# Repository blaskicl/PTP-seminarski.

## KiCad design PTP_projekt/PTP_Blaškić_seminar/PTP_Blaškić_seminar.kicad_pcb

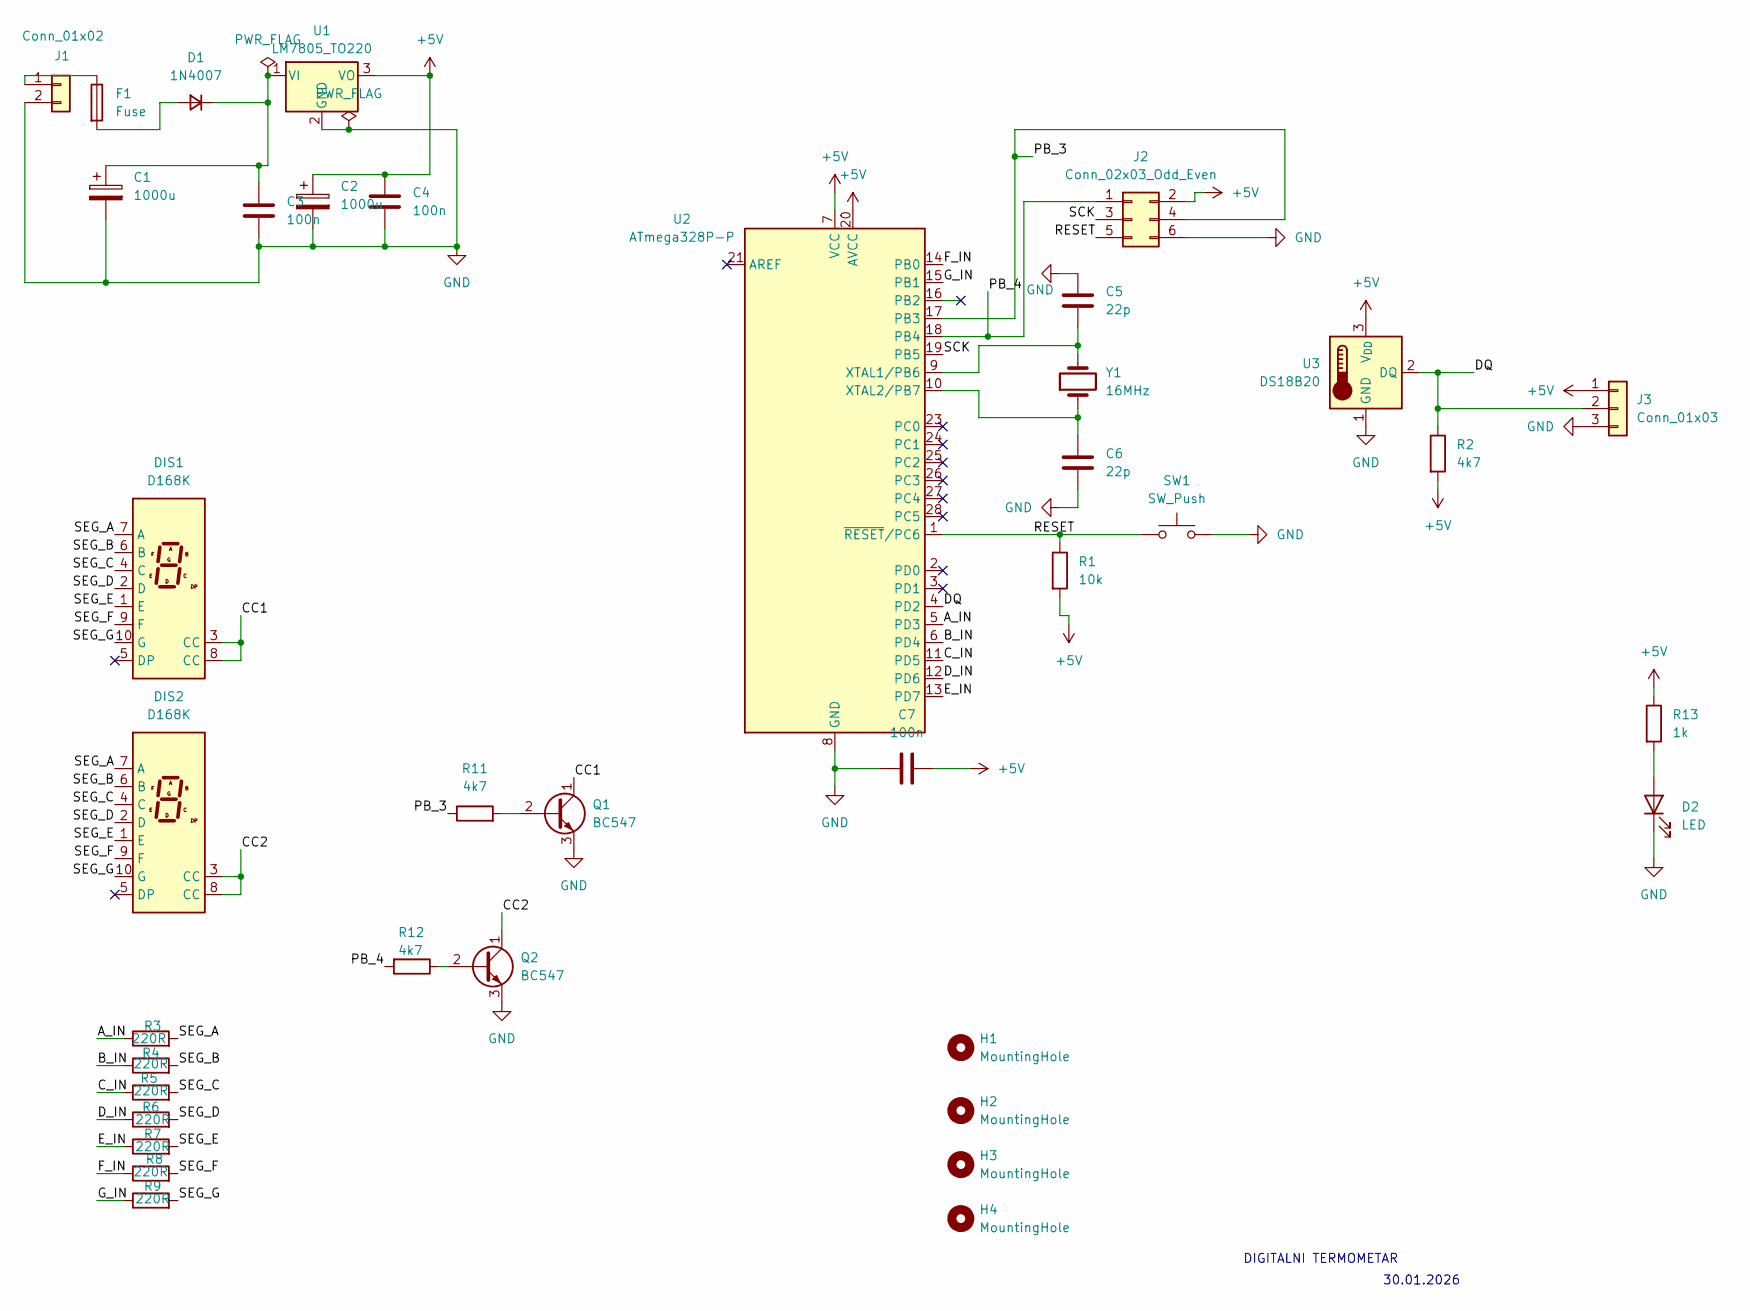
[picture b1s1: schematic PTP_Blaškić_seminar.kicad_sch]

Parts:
C1, C2: 1000u; CP_Radial_D10.0mm_P5.00mm; Manufacturers Part Numb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 UPM1V102MHD
C3, C4, C7: 100n; C_Disc_D5.0mm_W2.5mm_P5.00mm; Manufacturers Part Numb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 C315C104M5U5TA
C5, C6: 22p; C_Disc_D3.0mm_W1.6mm_P2.50mm; Manufacturers Part Numb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 RDE5C1H220J 0P1H03B
D1: 1N4007; D_DO-41_SOD81_P7.62mm_Horizontal; Manufacturers Part Numb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 1N4007-E3/54
D2: LED; LED_D5.0mm; Manufacturers Part Numb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 WP7113ID
DIS1, DIS2: D168K; D1X8K; Manufacturers Part Numb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 SC56-11EWA
F1: Fuse; Fuseholder_Cylinder-5x20mm_Bulgin_FX0457_Horizontal_Closed; Manufacturers Part Numb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 0218001.HXP
H1, H2, H3, H4: MountingHole; MountingHole_3.2mm_M3
J1: Conn_01x02; PinHeader_1x02_P2.54mm_Vertical; Manufacturers Part Numb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 TSW-102-07-G-S
J2: Conn_02x03_Odd_Even; PinHeader_2x03_P2.54mm_Vertical; Manufacturers Part Numb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 TSW-103-07-G-D
J3: Conn_01x03; PinHeader_1x03_P2.54mm_Vertical; Manufacturers Part Numb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 TSW-103-07-G-S
Q1, Q2: BC547; TO-92_Inline; Manufacturers Part Numb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 BC547B
R1: 10k; R_Axial_DIN0207_L6.3mm_D2.5mm_P10.16mm_Horizontal; Manufacturers Part Numb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 CFR-25JB-52-10K
R2, R11, R12: 4k7; R_Axial_DIN0207_L6.3mm_D2.5mm_P10.16mm_Horizontal; Manufacturers Part Numb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 CFR-25JB-52-4K7
R3, R4, R5, R6, R7, R8, R9: 220R; R_Axial_DIN0207_L6.3mm_D2.5mm_P10.16mm_Horizontal; Manufacturers Part Numb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 CFR-25JB-52-220R
R13: 1k; R_Axial_DIN0207_L6.3mm_D2.5mm_P10.16mm_Horizontal; Manufacturers Part Numb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 CFR-25JB-52-1K
SW1: SW_Push; SW_PUSH_6mm_H4.3mm; Manufacturers Part Numb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 B3F-1000
U1: LM7805_TO220; TO-220-3_Vertical; Manufacturers Part Numb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 L7805CV
U2: ATmega328P-P; DIP-28_W7.62mm; Manufacturers Part Numb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 ATMEGA328P-PU
U3: DS18B20; TO-92_Inline; Manufacturers Part Numb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 DS18B20+
Y1: 16MHz; Crystal_HC49-U_Vertical; Manufacturers Part Numb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 FA-238 16.0000MB-C3

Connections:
+5V: C2.1, C4.1, C7.2, J2.2, J3.1, R1.2, R2.2, R13.1, U1.3 (VO), U2.7 (VCC), U2.20 (AVCC), U3.3 (V_{DD})
/A_IN: R3.1, U2.5 (PD3)
/B_IN: R4.1, U2.6 (PD4)
/CC1: DIS1.3 (CC), DIS1.8 (CC), Q1.1 (C)
/CC2: DIS2.3 (CC), DIS2.8 (CC), Q2.1 (C)
/C_IN: R5.1, U2.11 (PD5)
/DQ: J3.2, R2.1, U2.4 (PD2), U3.2 (DQ)
/D_IN: R6.1, U2.12 (PD6)
/E_IN: R7.1, U2.13 (PD7)
/F_IN: R8.1, U2.14 (PB0)
/G_IN: R9.1, U2.15 (PB1)
/PB_3: J2.4, R11.1, U2.17 (PB3)
/PB_4: J2.1, R12.2, U2.18 (PB4)
/RESET: J2.5, R1.1, SW1.1, U2.1 (~RESET/PC6)
/SCK: J2.3, U2.19 (PB5)
/SEG_A: DIS1.7 (A), DIS2.7 (A), R3.2
/SEG_B: DIS1.6 (B), DIS2.6 (B), R4.2
/SEG_C: DIS1.4 (C), DIS2.4 (C), R5.2
/SEG_D: DIS1.2 (D), DIS2.2 (D), R6.2
/SEG_E: DIS1.1 (E), DIS2.1 (E), R7.2
/SEG_F: DIS1.9 (F), DIS2.9 (F), R8.2
/SEG_G: DIS1.10 (G), DIS2.10 (G), R9.2
GND: C1.2, C2.2, C3.2, C4.2, C5.1, C6.2, C7.1, D2.1 (K), J1.2, J2.6, J3.3, Q1.3 (E), Q2.3 (E), SW1.2, U1.2 (GND), U2.8 (GND), U2.22 (GND), U3.1 (GND)
unnamed: D1.2 (A), F1.2
unnamed: C1.1, C3.1, D1.1 (K), U1.1 (VI)
unnamed: D2.2 (A), R13.2
unnamed: F1.1, J1.1
unnamed: Q1.2 (B), R11.2
unnamed: Q2.2 (B), R12.1
unnamed: C5.2, U2.9 (XTAL1/PB6), Y1.2
unnamed: C6.1, U2.10 (XTAL2/PB7), Y1.1

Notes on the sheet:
DIGITALNI TERMOMETAR
30.01.2026

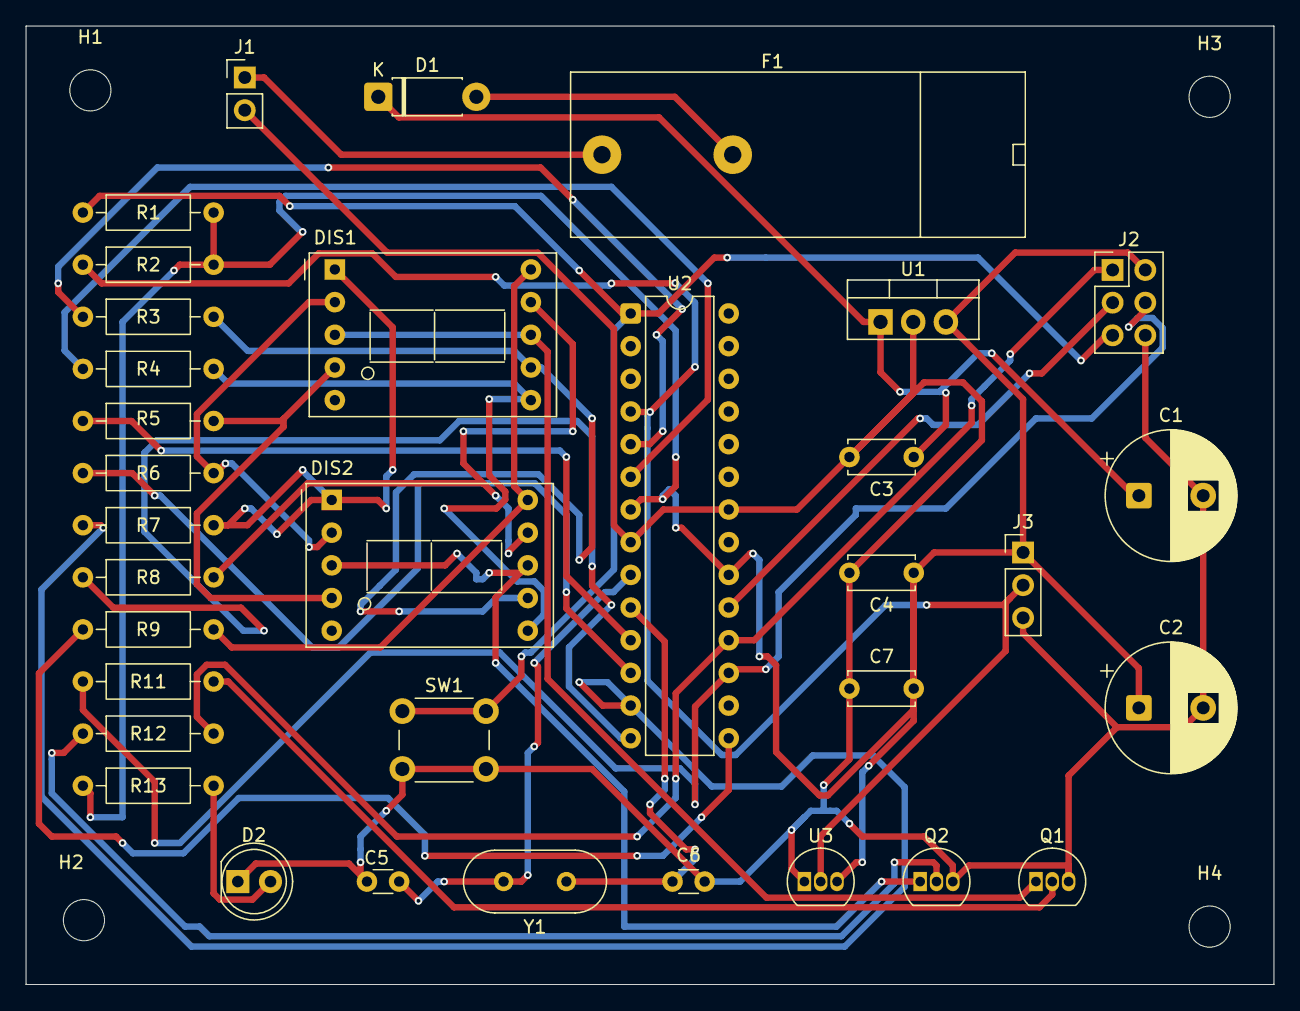
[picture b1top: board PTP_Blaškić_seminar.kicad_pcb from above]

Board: 2 copper layers, 97.0 x 74.5 mm, 38 parts (0 on the bottom side), 31 nets.
